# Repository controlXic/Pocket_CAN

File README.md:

# Control Xic CANFD Tool  

-STM32G474RET6 MCU  
-ST7796S TFT 480x320  
-TP FT6336  

A pocket-sized device for monitoring and transmitting CAN frames.  

Developed using **LVGL 9.2**, **STM32CubeIDE**, **KiCad**  

## Overview

The original goal of this research project was to develop a portable device capable of visualizing CAN FD frames on a 4-inch display.

The device provides the following features:

- **RX monitoring:** View received CAN frames.
- **TX transmission:** Transmit CAN frames.
- **Bitrate configuration:** Configure the bus bitrate (kbit/s).
- **RX display modes:** Choose between Trace and Static modes.
- **CAN filters:** Configure up to four CAN filters.
- **Bus statistics:** Monitor CAN bus statistics.
- **USB Serial interface:** Read and write data through a USB serial port (8N1, 115200 baud).

Device     

Tabs    

## Hardware and Design Notes

**CAN FD support was ultimately dropped** due to limitations related to the display size and overall user experience.

This project is based on an earlier hardware iteration that used a 4-inch Raspberry Pi display together with adapted libraries. This explains some of the design decisions behind the current PCB.

The original display's touchscreen was in poor condition, so it was replaced with an **MSP4030/4031 display**.

### Potential Improvements

There are several aspects of the hardware design that could be improved in a future revision:

- **PCB redesign:** A new PCB layout could make the device more compact. In particular, the overall Z-axis dimension could be reduced by approximately 10 mm.
- **Power switch placement:** The current position of the power switch is not ideal. As a result, the battery continues to drain even when the device appears to be switched off. This should be addressed in a future hardware revision.

- **Final Capabilities:** Furthermore, the microcontroller is operating at the limit of its capabilities—it is able to read CAN data with the bus at 100% load while simultaneously rendering it to the display. It might be advisable to limit the graphics memory allocation in `lv_conf.h`. This limitation also causes a "curtain" effect (tearing/stuttering) during screen refreshes, though it is not particularly distracting to the eye. 

- It is worth noting that reading and writing have been verified using professional tools such as PCAN, Kvaser, and CANoe. 

## Acknowledgements

Special thanks to [@lvgl](https://github.com/lvgl) for their excellent open-source work and for making LVGL available to the community.

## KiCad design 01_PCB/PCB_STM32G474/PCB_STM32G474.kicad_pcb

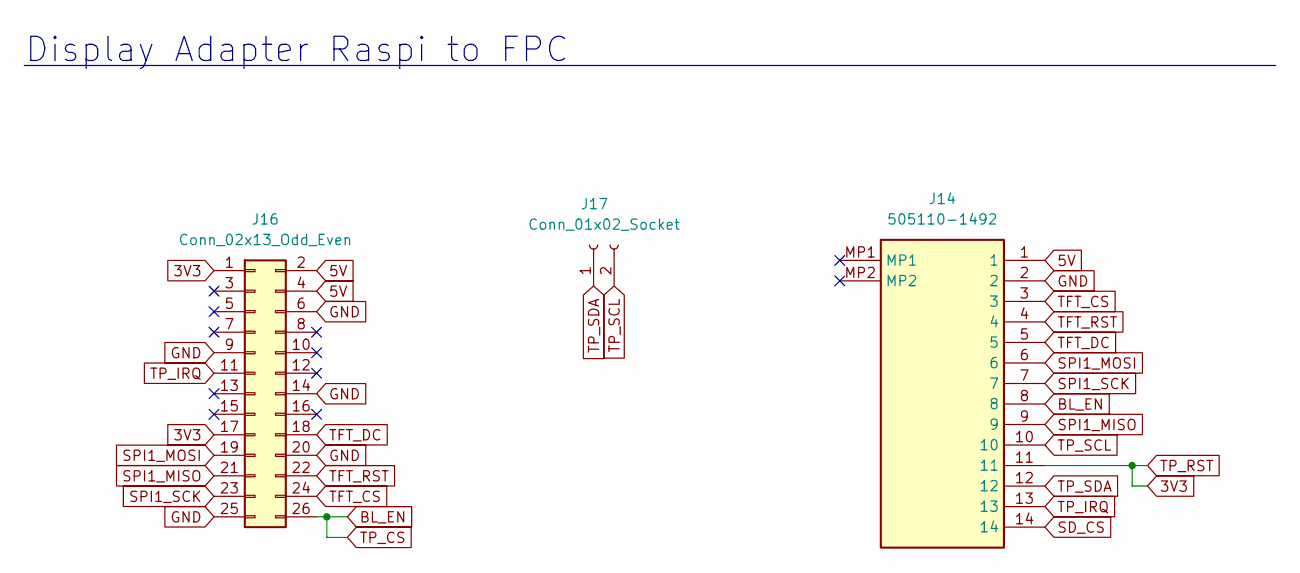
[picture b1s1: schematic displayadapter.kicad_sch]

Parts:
J14: 505110-1492; 5051101492; Manufacturer_Part_Number 505110-1492; Mouser Part Number 538-505110-1492
J16: Conn_02x13_Odd_Even; PinSocket_2x13_P2.54mm_Vertical
J17: Conn_01x02_Socket; PinSocket_1x02_P2.54mm_Vertical

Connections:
3V3: J14.11, J16.1, J16.17; also elsewhere on the board
5V: J14.1, J16.2, J16.4; also elsewhere on the board
BL_EN: J14.8, J16.26; also elsewhere on the board
GND: J14.2, J16.6, J16.9, J16.14, J16.20, J16.25; also elsewhere on the board
IO1: J14.12, J17.1; also elsewhere on the board
IO2: J14.10, J17.2; also elsewhere on the board
SD_CS: J14.14; also elsewhere on the board
SPI1_MISO: J14.9, J16.21; also elsewhere on the board
SPI1_MOSI: J14.6, J16.19; also elsewhere on the board
SPI1_SCK: J14.7, J16.23; also elsewhere on the board
TFT_CS: J14.3, J16.24; also elsewhere on the board
TFT_DC: J14.5, J16.18; also elsewhere on the board
TFT_RST: J14.4, J16.22; also elsewhere on the board
TP_IRQ: J14.13, J16.11; also elsewhere on the board

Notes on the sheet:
Display Adapter Raspi to FPC

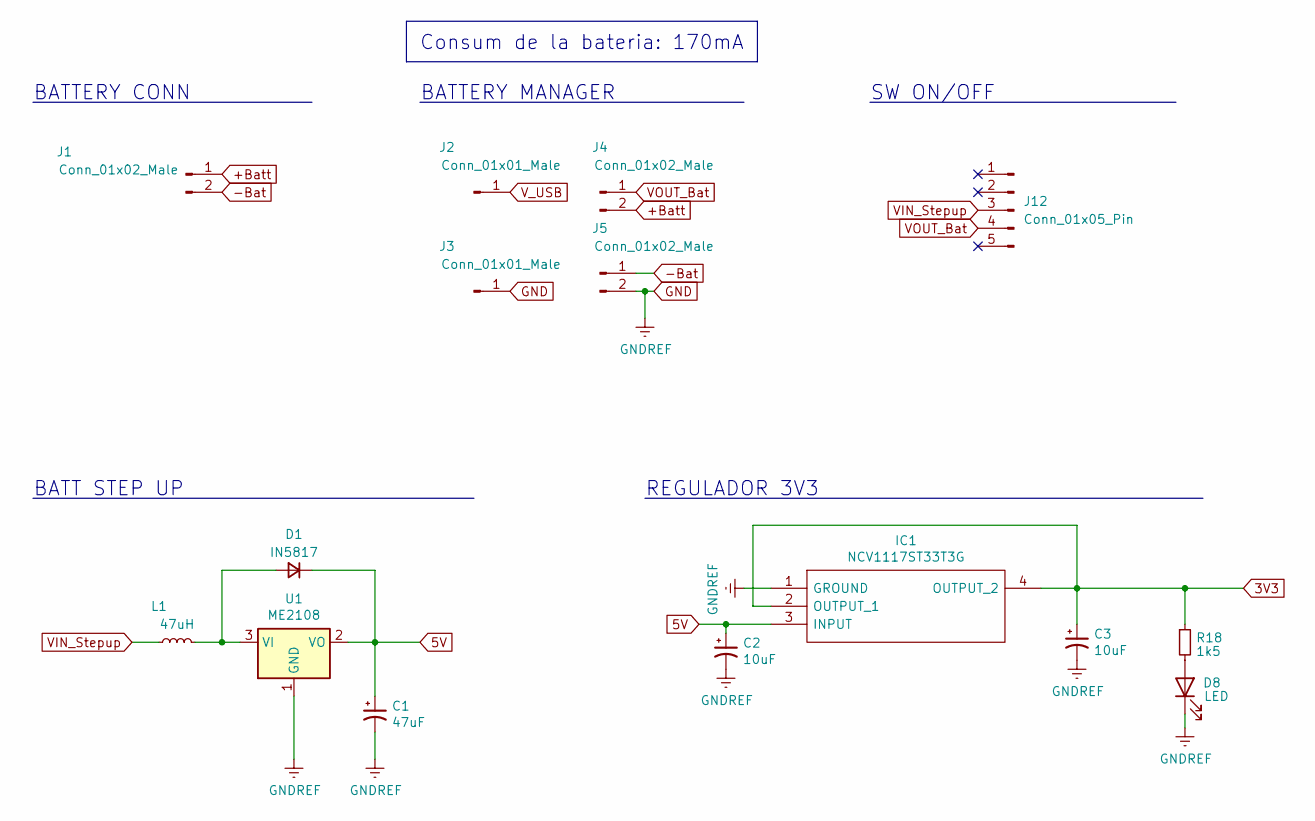
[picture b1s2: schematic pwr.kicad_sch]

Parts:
C1: 47uF; CP_EIA-3528-21_Kemet-B_Pad1.50x2.35mm_HandSolder
C2, C3: 10uF; CP_EIA-3216-18_Kemet-A
D1: IN5817; D_SMA
D8: LED; LED_1206_3216Metric
IC1: NCV1117ST33T3G; SOT-223-3_TabPin2; Manufacturer_Part_Number NCV1117ST33T3G; Mouser Part Number 863-NCV1117ST33T3G
J1: Conn_01x02_Male; PinHeader_1x02_P2.54mm_Horizontal
J2, J3: Conn_01x01_Male; PinSocket_1x01_P2.54mm_Vertical
J4, J5: Conn_01x02_Male; PinSocket_1x02_P2.54mm_Vertical
J12: Conn_01x05_Pin; PinHeader_1x05_P2.00mm_Vertical
L1: 47uH; L_Bourns_SRN6045TA
R18: 1k5; R_0805_2012Metric
U1: ME2108; SOT-89-3

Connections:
3V3: C3.1, IC1.2 (OUTPUT_1), IC1.4 (OUTPUT_2), R18.1; also elsewhere on the board
5V: C1.1, C2.1, D1.1 (K), IC1.3 (INPUT), U1.2 (VO); also elsewhere on the board
+Batt: J1.1, J4.2; also elsewhere on the board
-Bat: J1.2, J5.1
GND: C1.2, C2.2, C3.2, D8.1 (K), IC1.1 (GROUND), J3.1, J5.2, U1.1 (GND); also elsewhere on the board
unnamed: D1.2 (A), L1.2, U1.3 (VI)
unnamed: D8.2 (A), R18.2
VIN_Stepup: J12.3, L1.1
VOUT_Bat: J4.1, J12.4
V_USB: J2.1; also elsewhere on the board

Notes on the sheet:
Consum de la bateria: 170mA
REGULADOR 3V3
BATTERY CONN
BATTERY MANAGER
BATT STEP UP
SW ON/OFF

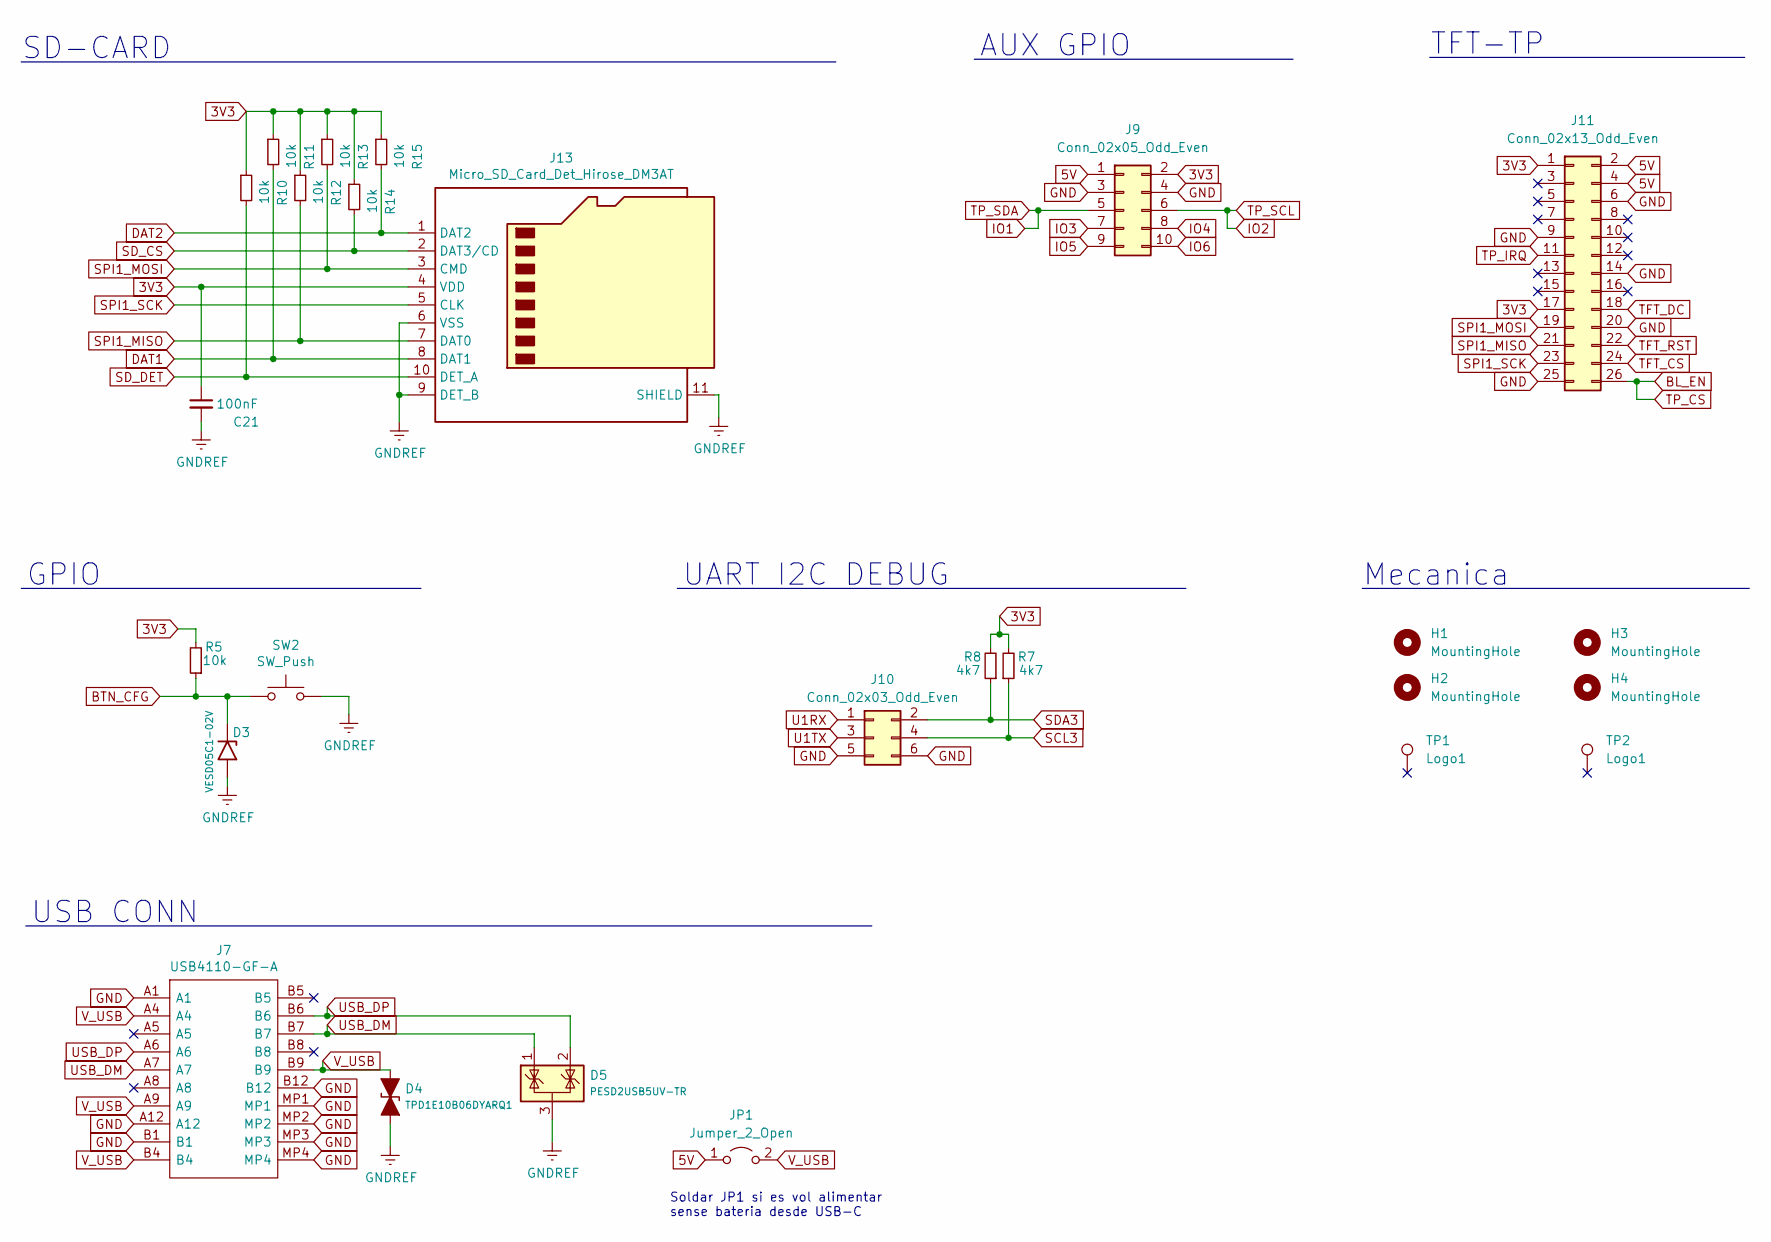
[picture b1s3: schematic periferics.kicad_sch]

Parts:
C21: 100nF; C_0603_1608Metric
D3: VESD05C1-02V; D_SOD-523
D4: TPD1E10B06DYARQ1; D_SOD-523
D5: PESD2USB5UV-TR; SOT-23
H1, H2, H3, H4: MountingHole; MountingHole_3.2mm_M3
J7: USB4110-GF-A; USB4110GFA; Manufacturer_Part_Number USB4110-GF-A; Mouser Part Number 640-USB4110-GF-A
J9: Conn_02x05_Odd_Even; PinHeader_2x05_P2.54mm_Horizontal
J10: Conn_02x03_Odd_Even; PinHeader_2x03_P2.54mm_Horizontal
J11: Conn_02x13_Odd_Even; PinHeader_2x13_P2.54mm_Vertical
J13: Micro_SD_Card_Det_Hirose_DM3AT; microSD_HC_Hirose_DM3AT-SF-PEJM5
JP1: Jumper_2_Open; SolderJumper-2_P1.3mm_Open_TrianglePad1.0x1.5mm
R5, R10, R11, R12, R13, R14, R15: 10k; R_0603_1608Metric
R7, R8: 4k7; R_0603_1608Metric
SW2: SW_Push; SW_SPST_CK_RS282G05A3
TP1, TP2: Logo1; cxic

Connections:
3V3: C21.1, J9.2, J11.1, J11.17, J13.4 (VDD), R5.2, R7.2, R8.2, R10.1, R11.1, R12.1, R13.1, R14.1, R15.1; also elsewhere on the board
5V: J9.1, J11.2, J11.4, JP1.1 (A); also elsewhere on the board
BL_EN: J11.26; also elsewhere on the board
BTN_CFG: D3.1 (A1), R5.1, SW2.1; also elsewhere on the board
DAT1: J13.8 (DAT1), R11.2
DAT2: J13.1 (DAT2), R15.2
GND: C21.2, D3.2 (A2), D4.2 (A2), D5.3 (A), J7.A1, J7.A12, J7.B1, J7.B12, J7.MP1, J7.MP2, J7.MP3, J7.MP4, J9.3, J9.4, J10.5, J10.6, J11.6, J11.9, J11.14, J11.20, J11.25, J13.6 (VSS), J13.9 (DET_B), J13.11 (SHIELD), SW2.2; also elsewhere on the board
IO1: J9.5; also elsewhere on the board
IO2: J9.6; also elsewhere on the board
IO3: J9.7; also elsewhere on the board
IO4: J9.8; also elsewhere on the board
IO5: J9.9; also elsewhere on the board
IO6: J9.10; also elsewhere on the board
SCL3: J10.4, R7.1; also elsewhere on the board
SDA3: J10.2, R8.1; also elsewhere on the board
SD_CS: J13.2 (DAT3/CD), R14.2; also elsewhere on the board
SD_DET: J13.10 (DET_A), R10.2; also elsewhere on the board
SPI1_MISO: J11.21, J13.7 (DAT0), R12.2; also elsewhere on the board
SPI1_MOSI: J11.19, J13.3 (CMD), R13.2; also elsewhere on the board
SPI1_SCK: J11.23, J13.5 (CLK); also elsewhere on the board
TFT_CS: J11.24; also elsewhere on the board
TFT_DC: J11.18; also elsewhere on the board
TFT_RST: J11.22; also elsewhere on the board
TP_IRQ: J11.11; also elsewhere on the board
U1RX: J10.1; also elsewhere on the board
U1TX: J10.3; also elsewhere on the board
USB_DM: D5.1 (K), J7.A7, J7.B7; also elsewhere on the board
USB_DP: D5.2 (K), J7.A6, J7.B6; also elsewhere on the board
V_USB: D4.1 (A1), J7.A4, J7.A9, J7.B4, J7.B9, JP1.2 (B); also elsewhere on the board

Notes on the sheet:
Soldar JP1 si es vol alimentar sense bateria desde USB-C
SD-CARD
UART I2C DEBUG
TFT-TP
AUX GPIO
USB CONN
Mecanica
GPIO

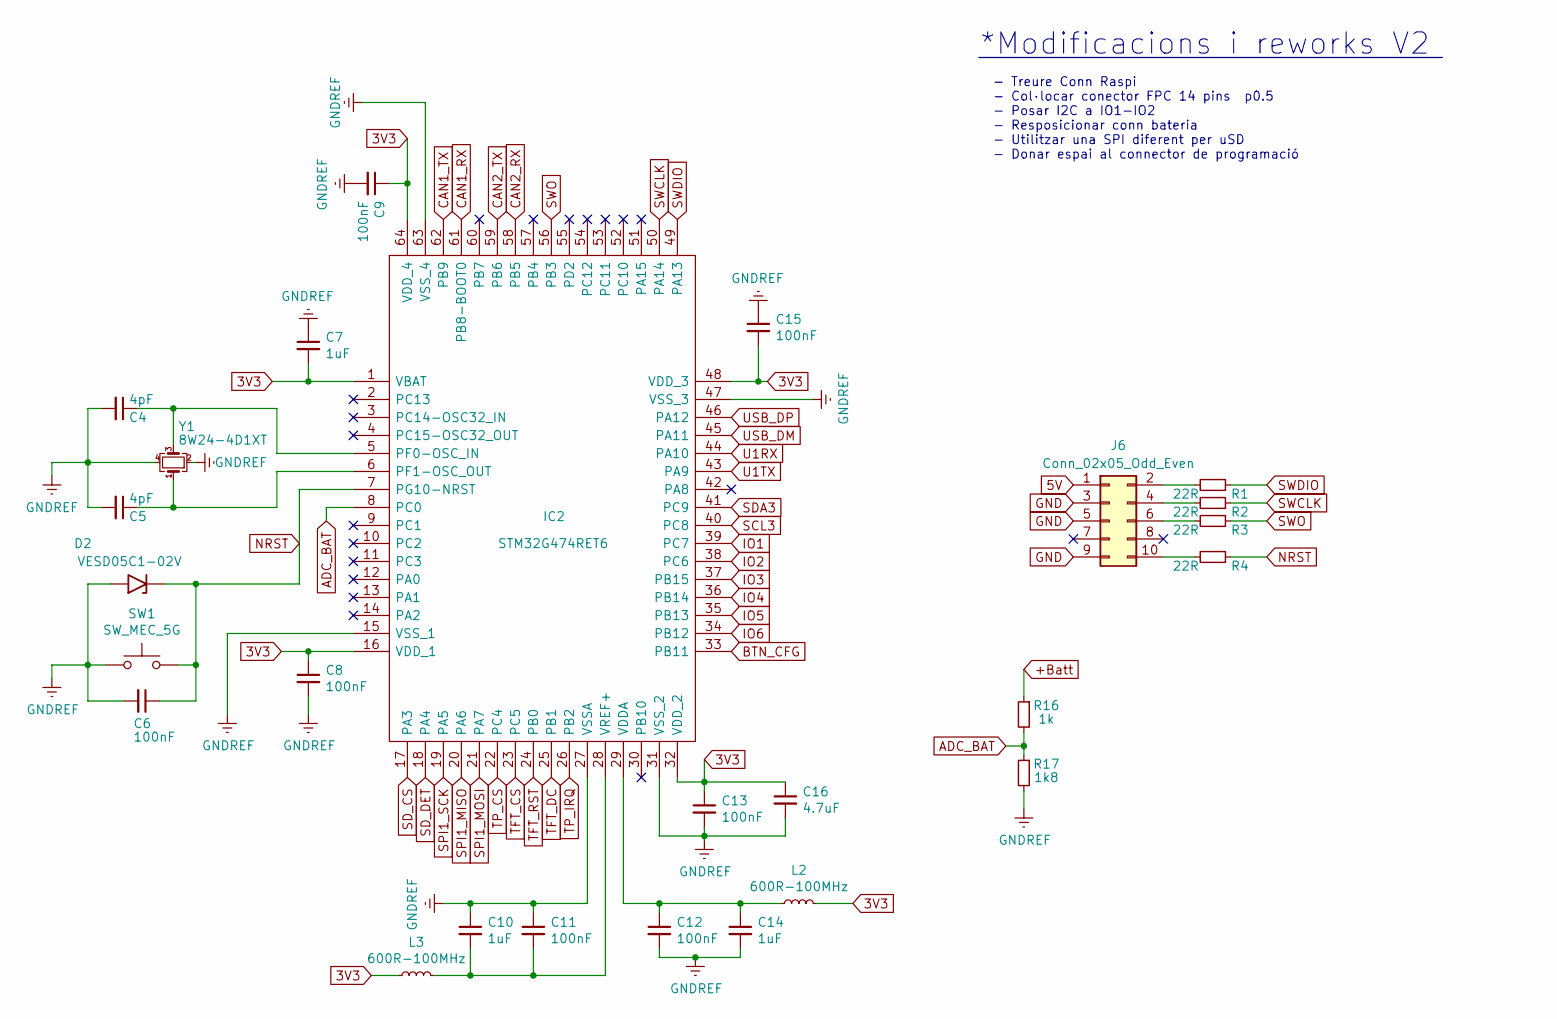
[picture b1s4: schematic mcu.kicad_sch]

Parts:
C4, C5: 4pF; C_0805_2012Metric
C6, C8, C9, C11, C12, C13, C15: 100nF; C_0603_1608Metric
C7, C10, C14: 1uF; C_0805_2012Metric
C16: 4.7uF; C_0805_2012Metric
D2: VESD05C1-02V; D_SOD-523
IC2: STM32G474RET6; QFP50P1200X1200X160-64N; Manufacturer_Part_Number STM32G474RET6; Mouser Part Number 511-STM32G474RET6
J6: Conn_02x05_Odd_Even; PinHeader_2x05_P1.27mm_Vertical
L2, L3: 600R-100MHz; C_0805_2012Metric
R1, R2, R3, R4: 22R; R_0603_1608Metric
R16: 1k; R_0603_1608Metric
R17: 1k8; R_0603_1608Metric
SW1: SW_MEC_5G; 223JMVAAR
Y1: 8W24-4D1XT; ABM8W480000MHZ6D1XT3

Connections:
3V3: C7.2, C8.1, C9.1, C13.1, C15.2, C16.1, IC2.1 (VBAT), IC2.16 (VDD_1), IC2.32 (VDD_2), IC2.48 (VDD_3), IC2.64 (VDD_4), L2.2, L3.1; also elsewhere on the board
5V: J6.1; also elsewhere on the board
+Batt: R16.1; also elsewhere on the board
ADC_BAT: IC2.8 (PC0), R16.2, R17.1
BL_EN: IC2.22 (PC4); also elsewhere on the board
BTN_CFG: IC2.33 (PB11); also elsewhere on the board
CAN1_RX: IC2.61 (PB8-BOOT0); also elsewhere on the board
CAN1_TX: IC2.62 (PB9); also elsewhere on the board
CAN2_RX: IC2.58 (PB5); also elsewhere on the board
CAN2_TX: IC2.59 (PB6); also elsewhere on the board
GND: C4.2, C5.2, C6.2, C7.1, C8.2, C9.2, C10.1, C11.1, C12.2, C13.2, C14.2, C15.1, C16.2, D2.2 (A2), IC2.15 (VSS_1), IC2.27 (VSSA), IC2.31 (VSS_2), IC2.47 (VSS_3), IC2.63 (VSS_4), J6.3, J6.5, J6.9, R17.2, SW1.2, Y1.2, Y1.4; also elsewhere on the board
IO1: IC2.39 (PC7); also elsewhere on the board
IO2: IC2.38 (PC6); also elsewhere on the board
IO3: IC2.37 (PB15); also elsewhere on the board
IO4: IC2.36 (PB14); also elsewhere on the board
IO5: IC2.35 (PB13); also elsewhere on the board
IO6: IC2.34 (PB12); also elsewhere on the board
NRST: C6.1, D2.1 (A1), IC2.7 (PG10-NRST), R4.1, SW1.1
unnamed: C4.1, IC2.5 (PF0-OSC_IN), Y1.3
unnamed: C5.1, IC2.6 (PF1-OSC_OUT), Y1.1
unnamed: C12.1, C14.1, IC2.29 (VDDA), L2.1
unnamed: C10.2, C11.2, IC2.28 (VREF+), L3.2
unnamed: J6.2, R1.2
unnamed: J6.4, R2.2
unnamed: J6.6, R3.2
unnamed: J6.10, R4.2
SCL3: IC2.40 (PC8); also elsewhere on the board
SDA3: IC2.41 (PC9); also elsewhere on the board
SD_CS: IC2.17 (PA3); also elsewhere on the board
SD_DET: IC2.18 (PA4); also elsewhere on the board
SPI1_MISO: IC2.20 (PA6); also elsewhere on the board
SPI1_MOSI: IC2.21 (PA7); also elsewhere on the board
SPI1_SCK: IC2.19 (PA5); also elsewhere on the board
SWCLK: IC2.50 (PA14), R2.1
SWDIO: IC2.49 (PA13), R1.1
SWO: IC2.56 (PB3), R3.1
TFT_CS: IC2.23 (PC5); also elsewhere on the board
TFT_DC: IC2.25 (PB1); also elsewhere on the board
TFT_RST: IC2.24 (PB0); also elsewhere on the board
TP_IRQ: IC2.26 (PB2); also elsewhere on the board
U1RX: IC2.44 (PA10); also elsewhere on the board
U1TX: IC2.43 (PA9); also elsewhere on the board
USB_DM: IC2.45 (PA11); also elsewhere on the board
USB_DP: IC2.46 (PA12); also elsewhere on the board

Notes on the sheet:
*Modificacions i reworks V2
- Treure Conn Raspi - Col·locar conector FPC 14 pins p0.5 - Posar I2C a IO1-IO2 - Resposicionar conn bateria - Utilitzar una SPI diferent per uSD - Donar espai al connector de programació

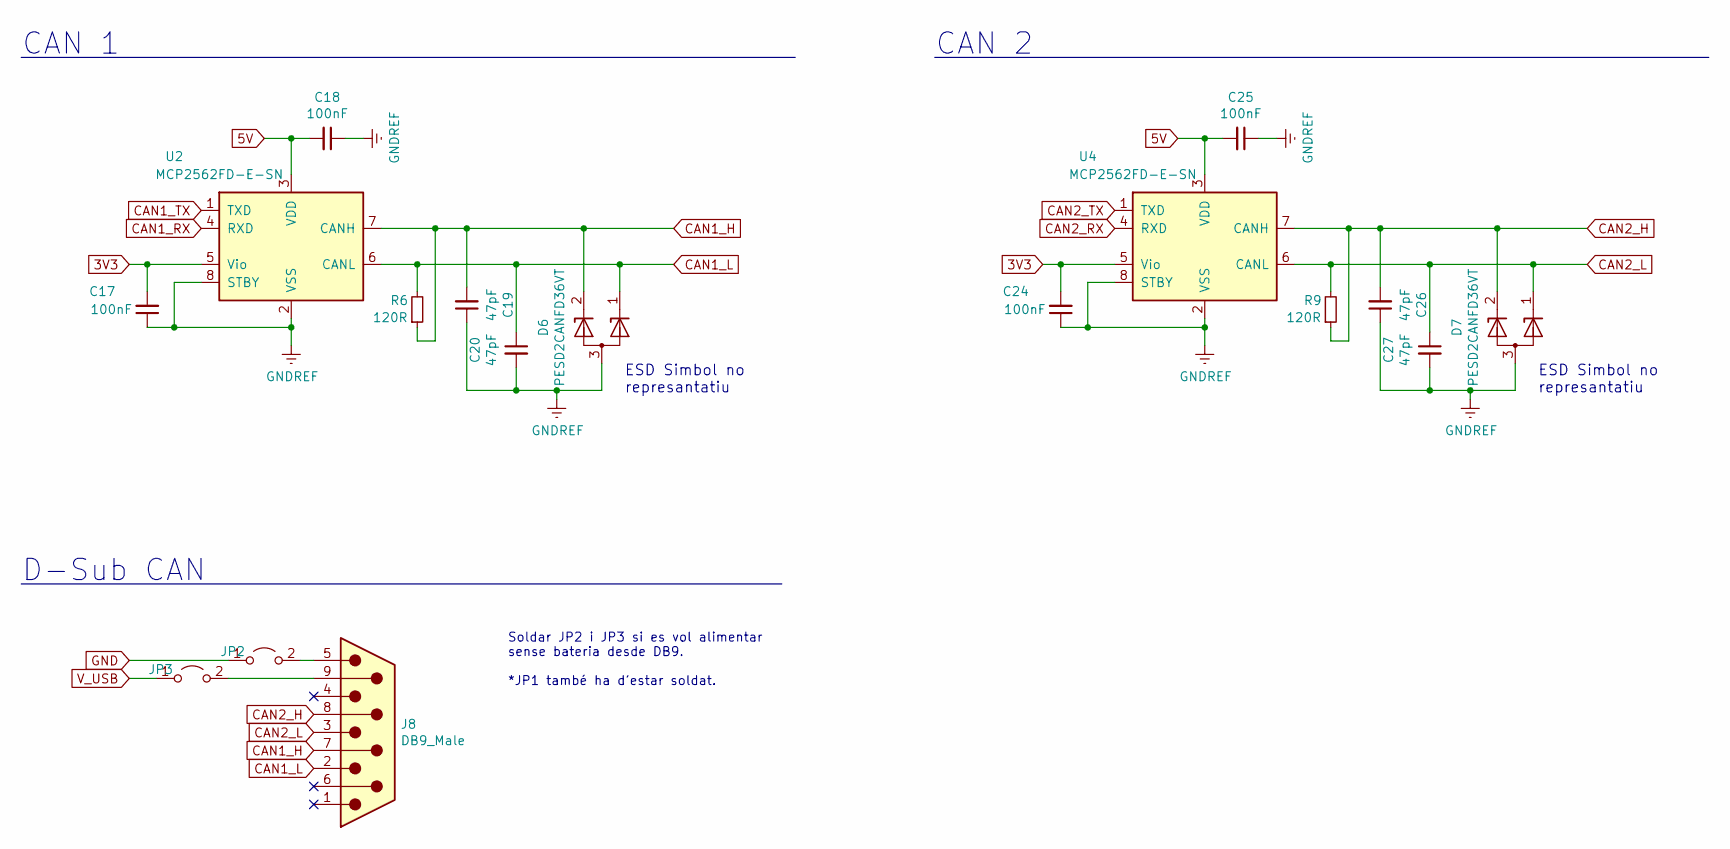
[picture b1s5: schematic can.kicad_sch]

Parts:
C17, C18, C24, C25: 100nF; C_0603_1608Metric
C19, C20, C26, C27: 47pF; C_0603_1608Metric
D6, D7: PESD2CANFD36VT; SOT-23
J8: DB9_Male; DSUB-9_Male_Horizontal_P2.77x2.84mm_EdgePinOffset7.70mm_Hou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
JP2, JP3: Jumper_2_Open; SolderJumper-2_P1.3mm_Open_TrianglePad1.0x1.5mm
R6, R9: 120R; R_0805_2012Metric
U2, U4: MCP2562FD-E-SN; SOIC-8_3.9x4.9mm_P1.27mm

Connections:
3V3: C17.2, C24.2, U2.5 (Vio), U4.5 (Vio); also elsewhere on the board
5V: C18.2, C25.2, U2.3 (VDD), U4.3 (VDD); also elsewhere on the board
CAN1_H: C19.2, D6.2 (K), J8.7, R6.1, U2.7 (CANH)
CAN1_L: C20.1, D6.1 (K), J8.2, R6.2, U2.6 (CANL)
CAN1_RX: U2.4 (RXD); also elsewhere on the board
CAN1_TX: U2.1 (TXD); also elsewhere on the board
CAN2_H: C26.2, D7.2 (K), J8.8, R9.1, U4.7 (CANH)
CAN2_L: C27.1, D7.1 (K), J8.3, R9.2, U4.6 (CANL)
CAN2_RX: U4.4 (RXD); also elsewhere on the board
CAN2_TX: U4.1 (TXD); also elsewhere on the board
GND: C17.1, C18.1, C19.1, C20.2, C24.1, C25.1, C26.1, C27.2, D6.3 (A), D7.3 (A), JP2.1 (A), U2.2 (VSS), U2.8 (STBY), U4.2 (VSS), U4.8 (STBY); also elsewhere on the board
unnamed: J8.5, JP2.2 (B)
unnamed: J8.9, JP3.2 (B)
V_USB: JP3.1 (A); also elsewhere on the board

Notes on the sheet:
ESD Simbol no represantatiu
Soldar JP2 i JP3 si es vol alimentar sense bateria desde DB9. *JP1 també ha d'estar soldat.
CAN 1
D-Sub CAN
CAN 2

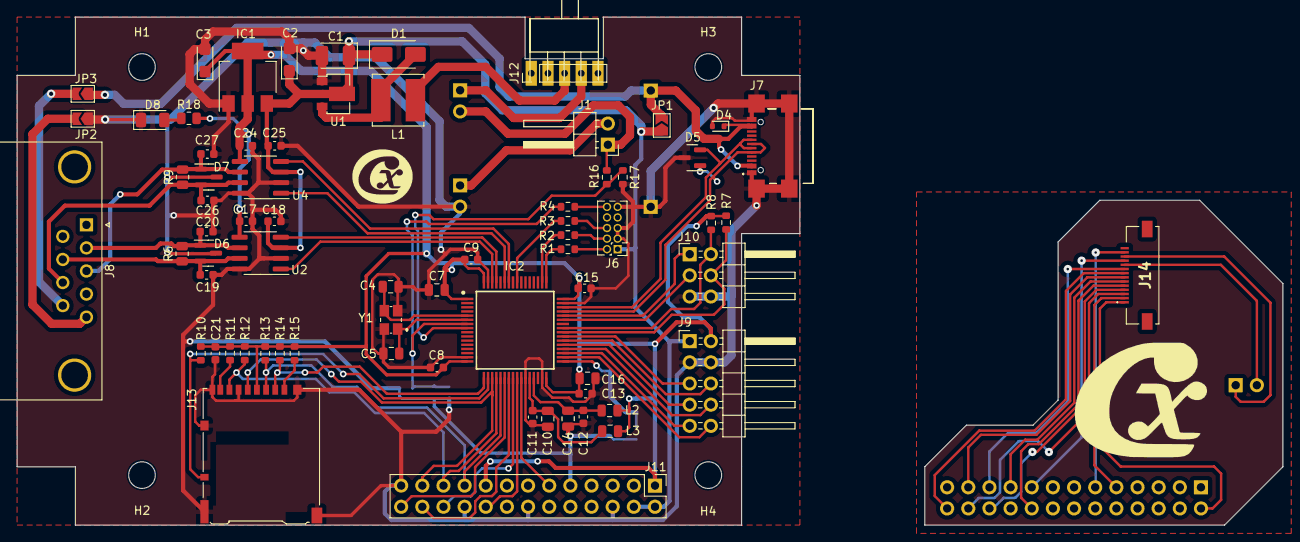
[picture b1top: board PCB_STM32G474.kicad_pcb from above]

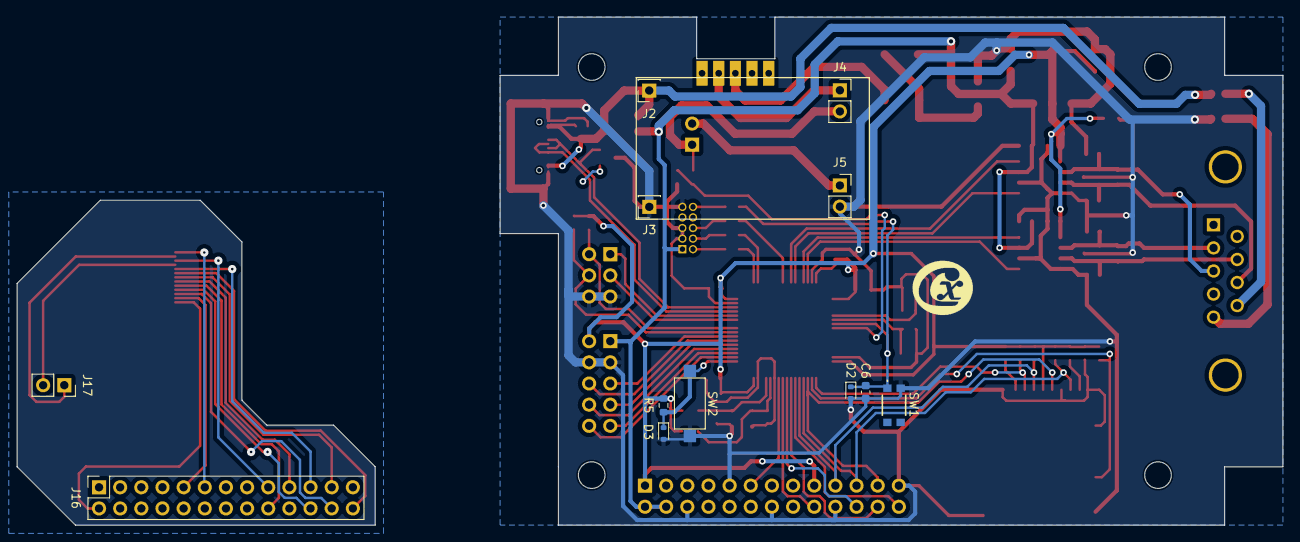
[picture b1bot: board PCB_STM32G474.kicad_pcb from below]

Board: 2 copper layers, 94.0 x 61.0 mm, 88 parts (13 on the bottom side), 58 nets.

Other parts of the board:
 : LOGO

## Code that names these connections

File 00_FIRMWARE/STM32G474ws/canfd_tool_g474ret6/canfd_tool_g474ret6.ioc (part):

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Mcu.Name=STM32G474R(B-C-E)Tx
Mcu.Package=LQFP64
Mcu.UserName=STM32G474RETx
PA10.Mode=Asynchronous
PA10.Signal=USART1_RX
PA11.Mode=Device
PA11.Signal=USB_DM
PA12.Mode=Device
PA12.Signal=USB_DP
PA13.Signal=SYS_JTMS-SWDIO
PA14.Signal=SYS_JTCK-SWCLK
PA3.GPIOParameters=GPIO_Label
PA3.GPIO_Label=SD_CS
PA3.Signal=GPIO_Output
PA4.GPIOParameters=GPIO_Label
PA4.GPIO_Label=SD_DET
PA4.Signal=GPIO_Output
PA5.GPIOParameters=GPIO_Speed,GPIO_PuPd
PA5.GPIO_PuPd=GPIO_PULLDOWN
PA5.GPIO_Speed=GPIO_SPEED_FREQ_VERY_HIGH
PA5.Mode=Full_Duplex_Master
PA5.Signal=SPI1_SCK
PA6.GPIOParameters=GPIO_Speed,GPIO_PuPd
PA6.GPIO_PuPd=GPIO_PULLDOWN
PA6.GPIO_Speed=GPIO_SPEED_FREQ_VERY_HIGH
PA6.Mode=Full_Duplex_Master
PA6.Signal=SPI1_MISO
PA7.GPIOParameters=GPIO_Speed,GPIO_PuPd
PA7.GPIO_PuPd=GPIO_PULLDOWN
PA7.GPIO_Speed=GPIO_SPEED_FREQ_VERY_HIGH
PA7.Mode=Full_Duplex_Master
PA7.Signal=SPI1_MOSI
PA9.Mode=Asynchronous
PA9.Signal=USART1_TX
PB0.GPIOParameters=PinState,GPIO_PuPd,GPIO_Label
PB0.GPIO_Label=TFT_RST
PB0.GPIO_PuPd=GPIO_PULLUP
PB0.PinState=GPIO_PIN_SET
PB0.Signal=GPIO_Output
PB1.GPIOParameters=GPIO_Speed,PinState,GPIO_Label
PB1.GPIO_Label=TFT_DC
PB1.GPIO_Speed=GPIO_SPEED_FREQ_VERY_HIGH
PB1.PinState=GPIO_PIN_SET
PB1.Signal=GPIO_Output
PB11.GPIOParameters=GPIO_PuPd,GPIO_Label
PB11.GPIO_Label=BTN_CFG
PB11.GPIO_PuPd=GPIO_PULLUP
PB11.Signal=GPIO_Input
PB2.GPIOParameters=GPIO_PuPd,GPIO_Label,GPIO_ModeDefaultEXTI
PB2.GPIO_Label=TP_IRQ
PB2.GPIO_ModeDefaultEXTI=GPIO_MODE_IT_FALLING
PB2.GPIO_PuPd=GPIO_PULLUP
PB2.Signal=GPXTI2
PB3.Signal=SYS_JTDO-SWO
PB5.Signal=FDCAN2_RX
PB6.Signal=FDCAN2_TX
PB8-BOOT0.GPIOParameters=GPIO_Speed,GPIO_PuPd,GPIO_FM8
PB8-BOOT0.GPIO_FM8=__NULL
PB8-BOOT0.GPIO_PuPd=GPIO_NOPULL
PB8-BOOT0.GPIO_Speed=GPIO_SPEED_FREQ_VERY_HIGH
PB8-BOOT0.Mode=FDCAN_Activate
PB8-BOOT0.Signal=FDCAN1_RX
PB9.GPIOParameters=GPIO_Speed
PB9.GPIO_Speed=GPIO_SPEED_FREQ_VERY_HIGH
PB9.Mode=FDCAN_Activate
PB9.Signal=FDCAN1_TX
PC0.GPIOParameters=GPIO_Label
PC0.GPIO_Label=ADC_BAT
PC0.Mode=IN6-Single-Ended
PC0.Signal=ADC1_IN6
PC4.GPIOParameters=GPIO_Label
PC4.GPIO_Label=TP_BL
PC4.Signal=GPIO_Output
PC5.GPIOParameters=GPIO_Speed,GPIO_Label
PC5.GPIO_Label=TFT_CS
PC5.GPIO_Speed=GPIO_SPEED_FREQ_VERY_HIGH
PC5.Signal=GPIO_Output
PC6.GPIOParameters=GPIO_Speed,GPIO_Pu
PC6.GPIO_Pu=GPIO_NOPULL
PC6.GPIO_Speed=GPIO_SPEED_FREQ_HIGH
PC6.Mode=I2C
PC6.Signal=I2C4_SCL
PC7.GPIOParameters=GPIO_Speed,GPIO_Pu
PC7.GPIO_Pu=GPIO_NOPULL
PC7.GPIO_Speed=GPIO_SPEED_FREQ_HIGH
PC7.Mode=I2C
PC7.Signal=I2C4_SDA
PC8.Signal=I2C3_SCL
PC9.Signal=I2C3_SDA
PF0-OSC_IN.Mode=HSE-External-Oscillator
PF0-OSC_IN.Signal=RCC_OSC_IN
PF1-OSC_OUT.Mode=HSE-External-Oscillator
PF1-OSC_OUT.Signal=RCC_OSC_OUT
PG10-NRST.GPIOParameters=GPIO_Label
PG10-NRST.GPIO_Label=NRST
PG10-NRST.Signal=EVENTOUT
RCC.HSE_VALUE=24000000
RCC.SYSCLKFreq_VALUE=160000000
RCC.SYSCLKSource=RCC_SYSCLKSOURCE_PLLCLK
board=custom
